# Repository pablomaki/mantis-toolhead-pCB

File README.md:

# Mantis_Toolhead_PCB

| ❗ NOTE          |
|:---------------------------|
| This alternative design is functionally the same as the one in main branch but a different layout, shape & connection points on PCB. |

## Description
This toolhead board was designed to be used with mantis toolhead mod for voron 3D printers.

The input is 16 pin molex microfit connector and outputs include
* 1 x 2 pin microfit/JST XH connector for Heater
* 1 x 2 pin microfit/JST XH connector for Thermistor
* 1 x 2 pin microfit/JST XH connector for Hotend fan
* 1 x 2 pin microfit/JST XH connector for X-endstop
* 1 x 2 pin microfit/JST XH connector for Magprobe/Klicky/Quickdraw
* 2 x 2 pin microfit/JST XH connector for Cooling fans (connected in parallel)
* 1 x 4 pin microfit connector for Extruder motor

This PCB is simply a breakout for the inputs from 16 pin connector so the user may decide where the outputs are actually used and stray from the original designed functions of the ports.

## BOM

* PCB
* 7 x 2 pin microfit pcb headers/2 pin JST XH connectors (You can use what you like, the holes are designed for microfit connectors so hole pitch is a bit high for JST XH but should work with careful soldering, note that there is no real need for using microfits for anything other than heater for which it is recommended due to higher current.)
* 1 x 4 pin microfit pcb header (JST-XH will not work here due to too small pitch)
* 1 x 16 pin microfit pcb header horizontal or vertical.

## Mounting

PCB can be mounted on the mantis carriage with the two m3 holes on the board as shown in the images below.

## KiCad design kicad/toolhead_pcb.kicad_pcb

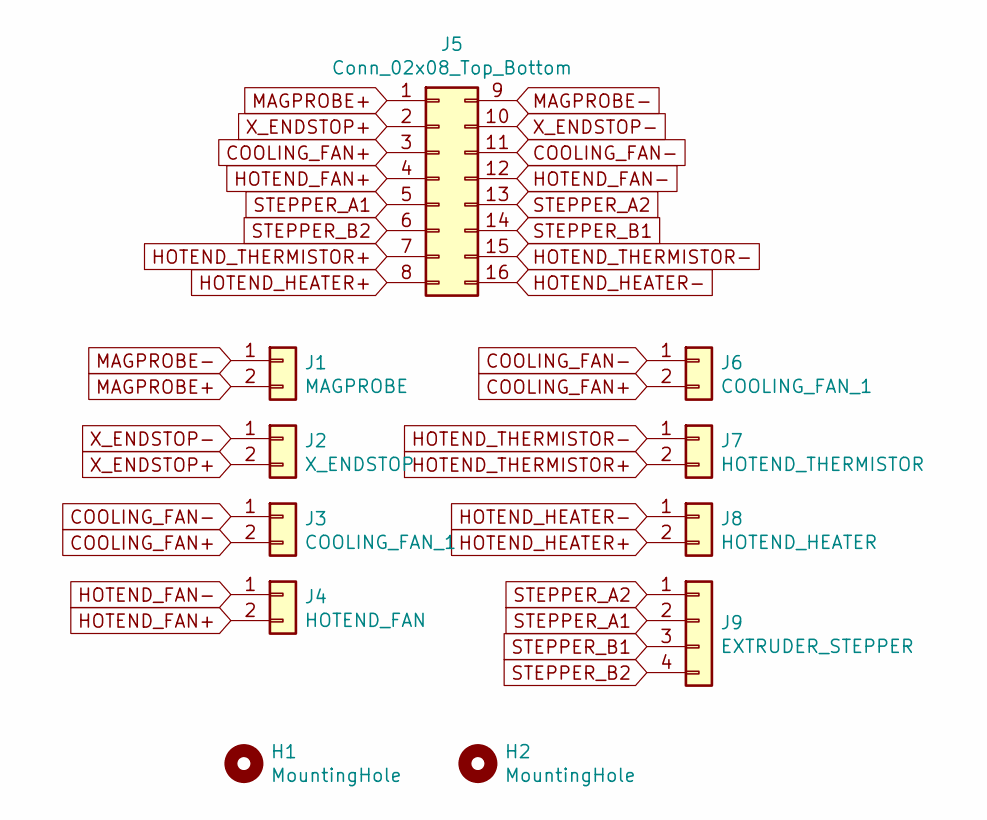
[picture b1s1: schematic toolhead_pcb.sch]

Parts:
H1, H2: MountingHole; MountingHole_3.2mm_M3_ISO7380
J1: MAGPROBE; JST_XH_B2B-XH-A_1x02_P2.50mm_Vertical
J2: X_ENDSTOP; JST_XH_B2B-XH-A_1x02_P2.50mm_Vertical
J3, J6: COOLING_FAN_1; JST_XH_B2B-XH-A_1x02_P2.50mm_Vertical
J4: HOTEND_FAN; JST_XH_B2B-XH-A_1x02_P2.50mm_Vertical
J5: Conn_02x08_Top_Bottom; Molex_Micro-Fit_3.0_43045-1600_2x08_P3.00mm_Horizontal
J7: HOTEND_THERMISTOR; JST_XH_B2B-XH-A_1x02_P2.50mm_Vertical
J8: HOTEND_HEATER; Molex_Micro-Fit_3.0_43650-0200_1x02_P3.00mm_Horizontal
J9: EXTRUDER_STEPPER; JST_XH_B4B-XH-A_1x04_P2.50mm_Vertical

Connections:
COOLING_FAN+: J3.2, J5.3, J6.2
COOLING_FAN-: J3.1, J5.11, J6.1
HOTEND_FAN+: J4.2, J5.4
HOTEND_FAN-: J4.1, J5.12
HOTEND_HEATER+: J5.8, J8.2
HOTEND_HEATER-: J5.16, J8.1
HOTEND_THERMISTOR+: J5.7, J7.2
HOTEND_THERMISTOR-: J5.15, J7.1
MAGPROBE+: J1.2, J5.1
MAGPROBE-: J1.1, J5.9
STEPPER_A1: J5.5, J9.2
STEPPER_A2: J5.13, J9.1
STEPPER_B1: J5.14, J9.3
STEPPER_B2: J5.6, J9.4
X_ENDSTOP+: J2.2, J5.2
X_ENDSTOP-: J2.1, J5.10

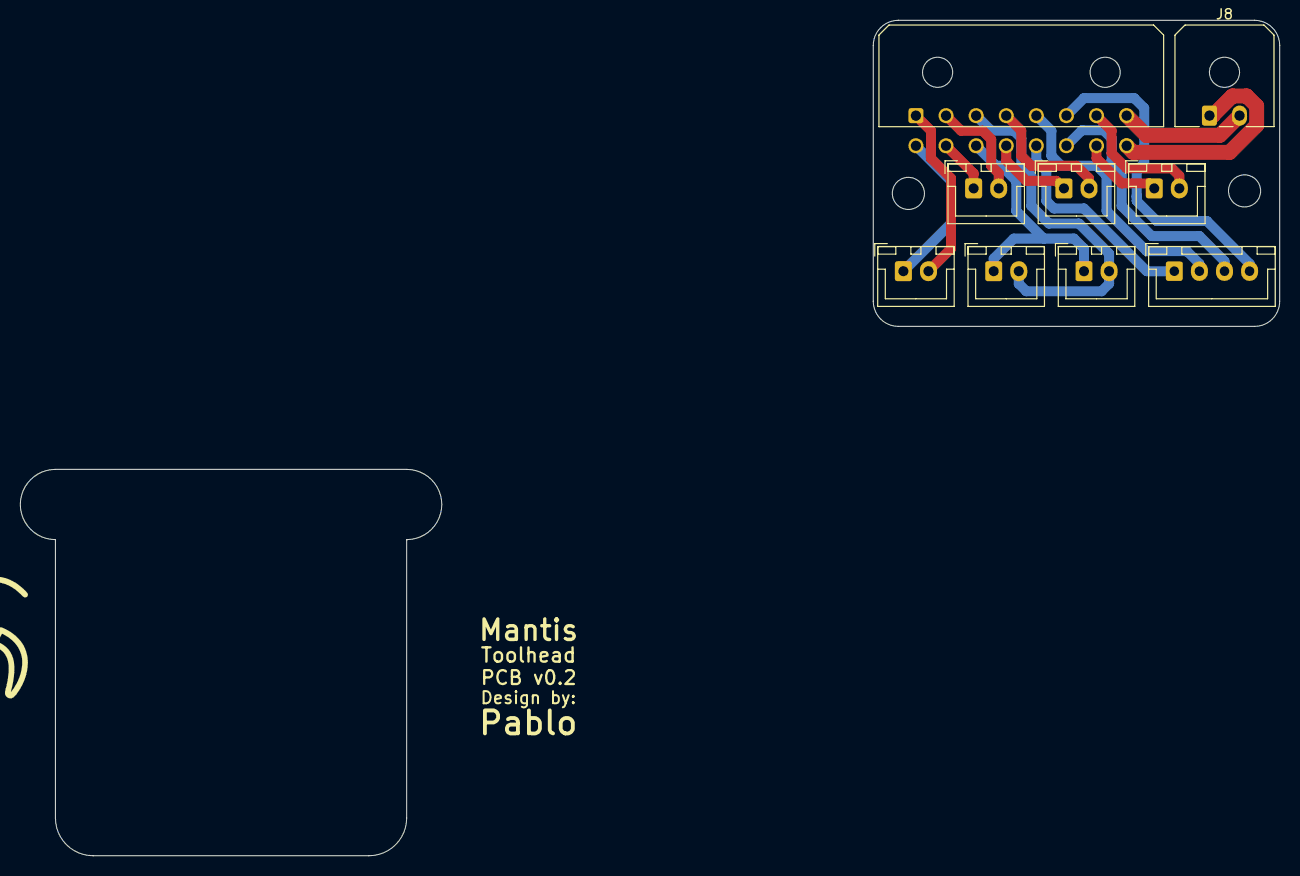
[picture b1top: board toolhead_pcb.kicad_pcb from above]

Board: 2 copper layers, 40.5 x 30.5 mm, 11 parts (0 on the bottom side), 16 nets.

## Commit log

2023-05-07 Initial push of exiting stuff
2023-05-09 Organize and add content to README
2023-05-09 Push alternative design for board
2023-05-09 Add note and screenshot about alternative design
2023-05-09 Fix README.md
2025-01-17 Create LICENSE
